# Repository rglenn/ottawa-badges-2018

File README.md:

# ottawa-badges-2018
Maker badges for Maker Faire Ottawa 2018

More information is available on the [wiki](https://github.com/rglenn/ottawa-badges-2018/wiki) - please check there!

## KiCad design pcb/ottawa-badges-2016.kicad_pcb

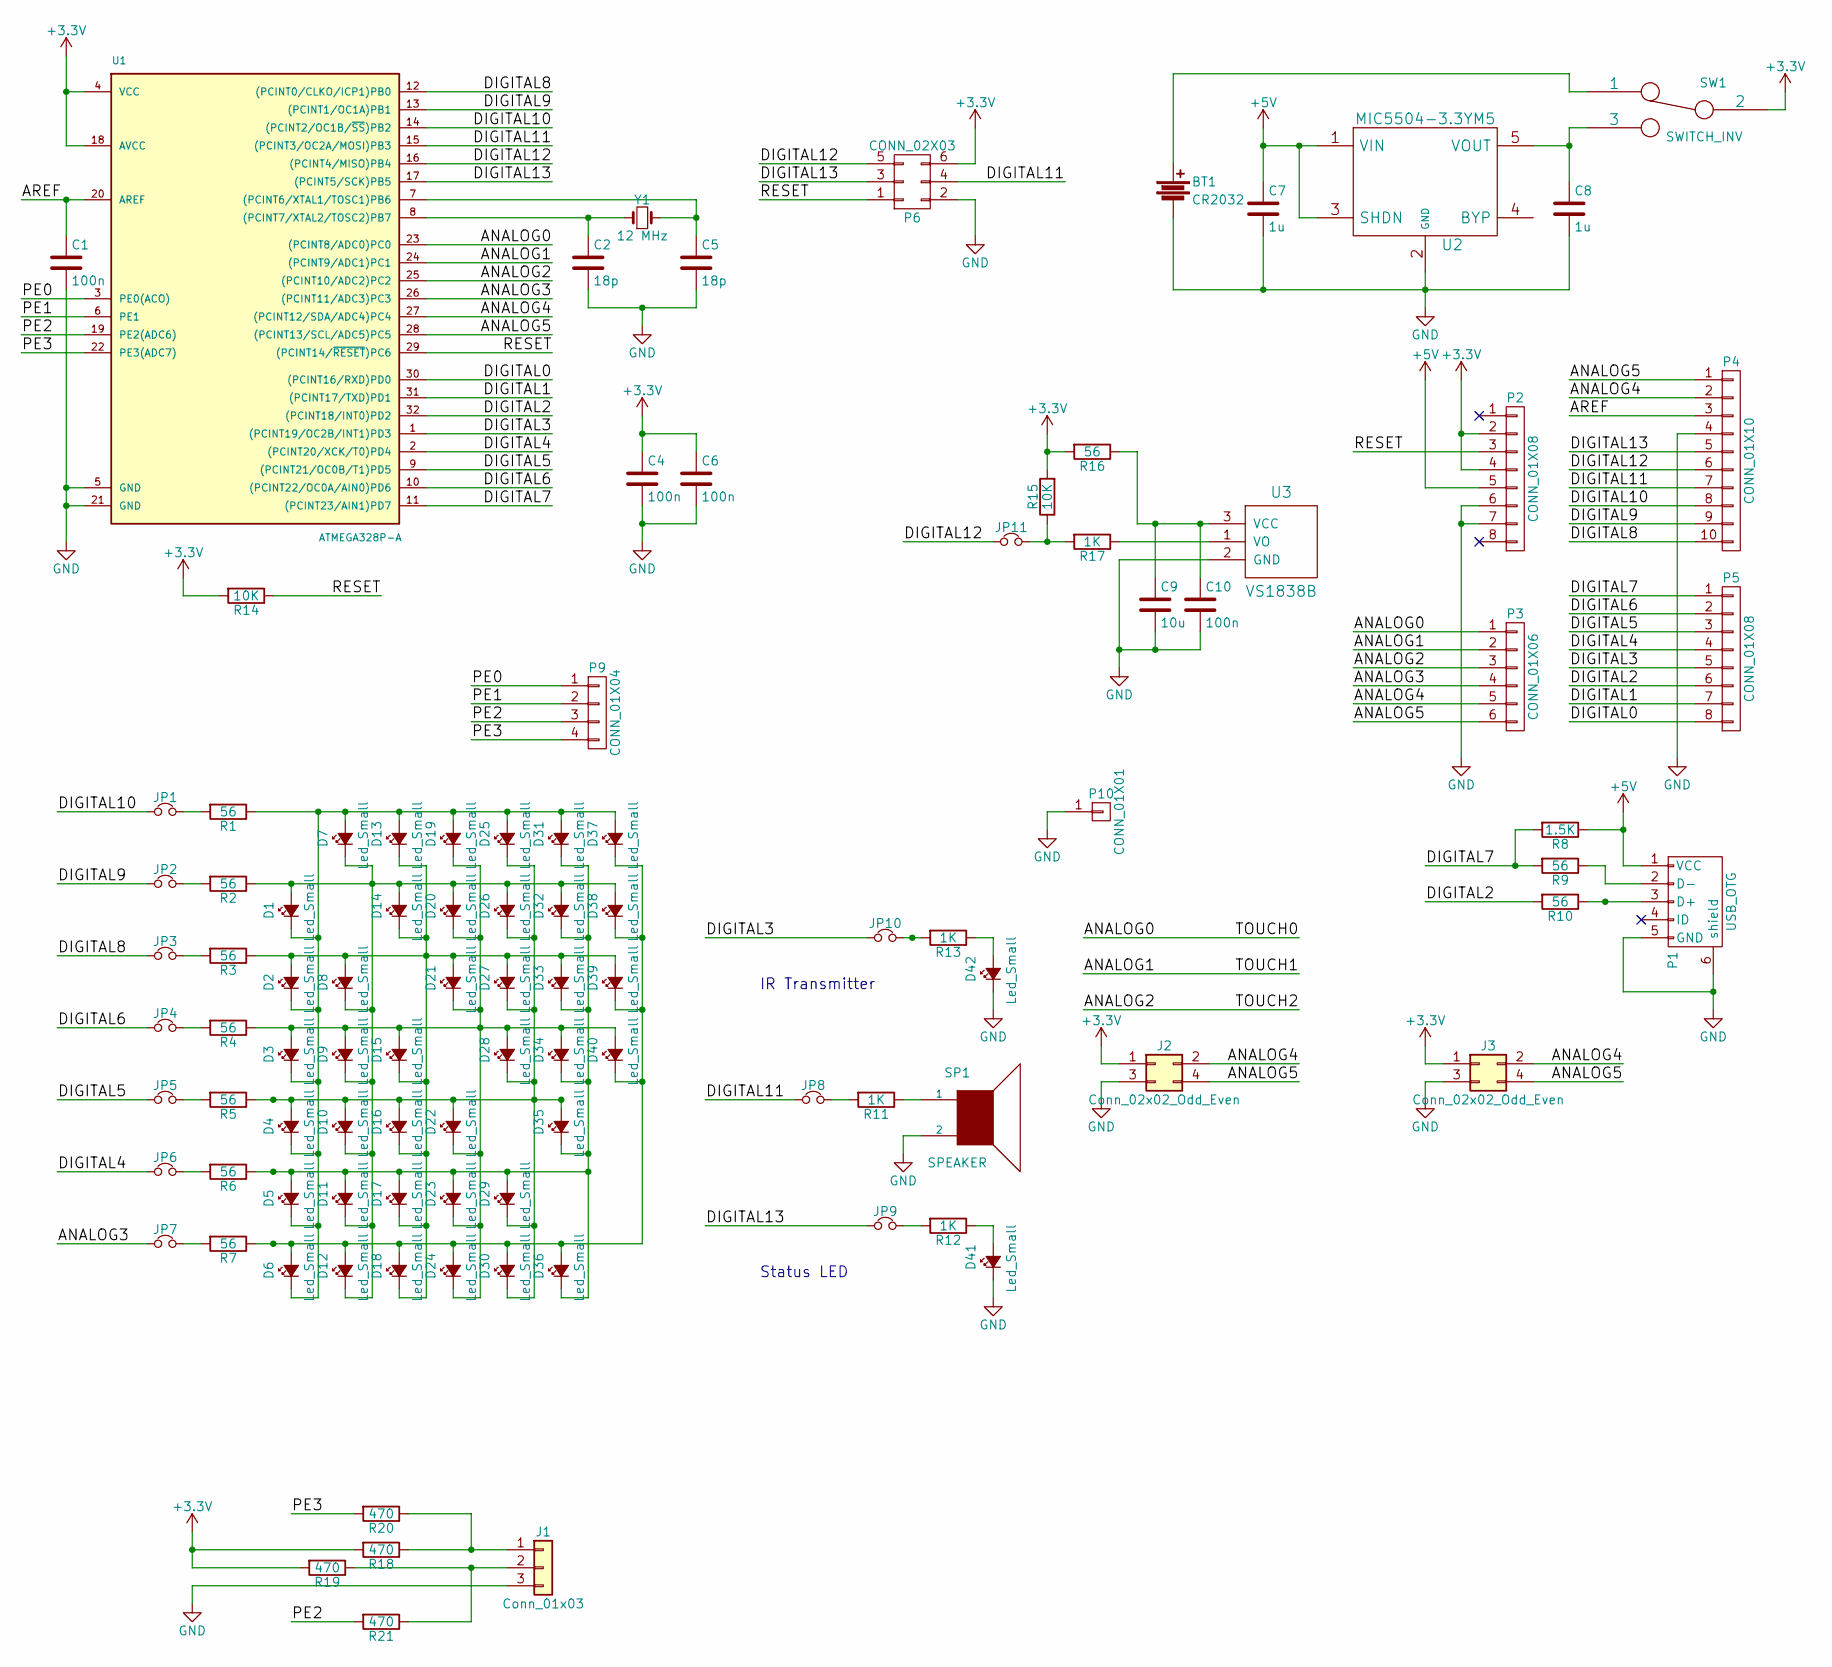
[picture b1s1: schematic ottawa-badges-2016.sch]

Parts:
BT1: CR2032; CR2032-SHRAPNEL
C1, C4, C6, C10: 100n; C_0603
C2, C5: 18p; C_0603
C7, C8: 1u; C_0603
C9: 10u; C_0805
D1, D2, D3, D4, D5, D6, D7, D8, D9, D10, D11, D12, D13, D14, D15, D16, D17, D18, D19, D20, D21, D22, D23, D24, D25, D26, D27, D28, D29, D30, D31, D32, D33, D34, D35, D36, D37, D38, D39, D40, D41: Led_Small; LED_0603
D42: Led_Small; LED_0805
J1: Conn_01x03; Pin_Header_Straight_1x03_Pitch2.54mm
J2, J3: Conn_02x02_Odd_Even; Pin_Header_Straight_2x02_Pitch2.54mm
JP1, JP2, JP3, JP4, JP5, JP6, JP7, JP8, JP9, JP10, JP11: Jumper_NC_Small; SJ2
P1: USB_OTG; 10118192-0001LF
P2, P5: CONN_01X08; Socket_Strip_Straight_1x08
P3: CONN_01X06; Socket_Strip_Straight_1x06
P4: CONN_01X10; Socket_Strip_Straight_1x10
P6: CONN_02X03; Socket_Strip_Straight_2x03
P9: CONN_01X04; Socket_Strip_Straight_1x04
P10: CONN_01X01; MountingHole_4mm_Pad_Via
R1, R2, R3, R4, R5, R6, R7, R9, R10, R16: 56; R_0603
R8: 1.5K; R_0603
R11, R12, R13, R17: 1K; R_0603
R14, R15: 10K; R_0603
R18, R19, R20, R21: 470; R_0603
SP1: SPEAKER; Buzzer_12x9.5RM7.6
SW1: SWITCH_INV; MK-12C02
U1: ATMEGA328P-A; TQFP-32_7x7mm_Pitch0.8mm
U2: MIC5504-3.3YM5; SOT-23-5
U3: VS1838B; VS1838B-HORIZ
Y1: 12 MHz; crystal_FA238-TSX3225

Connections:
+3V3: C4.1, C6.1, J2.1, J3.1, P2.2, P2.4, P6.6, R14.2, R15.2, R16.2, R18.2, R19.2, SW1.2, U1.4 (VCC), U1.18 (AVCC)
+5V: C7.1, P1.1 (VCC), P2.5, R8.1, U2.1 (VIN), U2.3 (SHDN)
/ANALOG0: P3.1, U1.23 ((PCINT8/ADC0)PC0)
/ANALOG1: P3.2, U1.24 ((PCINT9/ADC1)PC1)
/ANALOG2: P3.3, U1.25 ((PCINT10/ADC2)PC2)
/ANALOG3: JP7.1, P3.4, U1.26 ((PCINT11/ADC3)PC3)
/ANALOG4: J2.2, J3.2, P3.5, P4.2, U1.27 ((PCINT12/SDA/ADC4)PC4)
/ANALOG5: J2.4, J3.4, P3.6, P4.1, U1.28 ((PCINT13/SCL/ADC5)PC5)
/AREF: C1.1, P4.3, U1.20 (AREF)
/DIGITAL0: P5.8, U1.30 ((PCINT16/RXD)PD0)
/DIGITAL1: P5.7, U1.31 ((PCINT17/TXD)PD1)
/DIGITAL2: P5.6, R10.2, U1.32 ((PCINT18/INT0)PD2)
/DIGITAL3: JP10.1, P5.5, U1.1 ((PCINT19/OC2B/INT1)PD3)
/DIGITAL4: JP6.1, P5.4, U1.2 ((PCINT20/XCK/T0)PD4)
/DIGITAL5: JP5.1, P5.3, U1.9 ((PCINT21/OC0B/T1)PD5)
/DIGITAL6: JP4.1, P5.2, U1.10 ((PCINT22/OC0A/AIN0)PD6)
/DIGITAL7: P5.1, R8.2, R9.2, U1.11 ((PCINT23/AIN1)PD7)
/DIGITAL8: JP3.1, P4.10, U1.12 ((PCINT0/CLKO/ICP1)PB0)
/DIGITAL9: JP2.1, P4.9, U1.13 ((PCINT1/OC1A)PB1)
/DIGITAL10: JP1.1, P4.8, U1.14 ((PCINT2/OC1B/~SS~)PB2)
/DIGITAL11: JP8.1, P4.7, P6.4, U1.15 ((PCINT3/OC2A/MOSI)PB3)
/DIGITAL12: JP11.1, P4.6, P6.5, U1.16 ((PCINT4/MISO)PB4)
/DIGITAL13: JP9.1, P4.5, P6.3, U1.17 ((PCINT5/SCK)PB5)
/PE0: P9.1, U1.3 (PE0(ACO))
/PE1: P9.2, U1.6 (PE1)
/PE2: P9.3, R21.2, U1.19 (PE2(ADC6))
/PE3: P9.4, R20.2, U1.22 (PE3(ADC7))
/RESET: P2.3, P6.1, R14.1, U1.29 ((PCINT14/~RESET~)PC6)
GND: BT1.2, C1.2, C2.2, C4.2, C5.2, C6.2, C7.2, C8.2, C9.2, C10.2, D41.1 (K), D42.1 (K), J1.3, J2.3, J3.3, P1.5 (GND), P1.6 (shield), P2.6, P2.7, P4.4, P6.2, P10.1, SP1.2, U1.5 (GND), U1.21 (GND), U2.2 (GND), U3.2 (GND)
unnamed: BT1.1, SW1.1
unnamed: C2.1, U1.8 ((PCINT7/XTAL2/TOSC2)PB7), Y1.1
unnamed: C5.1, U1.7 ((PCINT6/XTAL1/TOSC1)PB6), Y1.2
unnamed: C8.1, SW1.3, U2.5 (VOUT)
unnamed: C9.1, C10.1, R16.1, U3.3 (VCC)
unnamed: D1.1 (K), D2.1 (K), D3.1 (K), D4.1 (K), D5.1 (K), D6.1 (K), D7.2 (A), D13.2 (A), D19.2 (A), D25.2 (A), D31.2 (A), D37.2 (A), R1.1
unnamed: D1.2 (A), D7.1 (K), D8.1 (K), D9.1 (K), D10.1 (K), D11.1 (K), D12.1 (K), D14.2 (A), D20.2 (A), D26.2 (A), D32.2 (A), D38.2 (A), R2.1
unnamed: D4.2 (A), D10.2 (A), D16.2 (A), D22.2 (A), D25.1 (K), D26.1 (K), D27.1 (K), D28.1 (K), D29.1 (K), D30.1 (K), D35.2 (A), R5.1
unnamed: D5.2 (A), D11.2 (A), D17.2 (A), D23.2 (A), D29.2 (A), D31.1 (K), D32.1 (K), D33.1 (K), D34.1 (K), D35.1 (K), D36.1 (K), R6.1
unnamed: D6.2 (A), D12.2 (A), D18.2 (A), D24.2 (A), D30.2 (A), D36.2 (A), D37.1 (K), D38.1 (K), D39.1 (K), D40.1 (K), R7.1
unnamed: D2.2 (A), D8.2 (A), D13.1 (K), D14.1 (K), D15.1 (K), D16.1 (K), D17.1 (K), D18.1 (K), D21.2 (A), D27.2 (A), D33.2 (A), D39.2 (A), R3.1
unnamed: D3.2 (A), D9.2 (A), D15.2 (A), D19.1 (K), D20.1 (K), D21.1 (K), D22.1 (K), D23.1 (K), D24.1 (K), D28.2 (A), D34.2 (A), D40.2 (A), R4.1
unnamed: D41.2 (A), R12.1
unnamed: D42.2 (A), R13.1
unnamed: J1.1, R18.1, R20.1
unnamed: J1.2, R19.1, R21.1
unnamed: JP1.2, R1.2
unnamed: JP2.2, R2.2
unnamed: JP3.2, R3.2
unnamed: JP4.2, R4.2
unnamed: JP5.2, R5.2
unnamed: JP6.2, R6.2
unnamed: JP7.2, R7.2
unnamed: JP8.2, R11.2
unnamed: JP9.2, R12.2
unnamed: JP10.2, R13.2
unnamed: JP11.2, R15.1, R17.2
unnamed: P1.2 (D-), R9.1
unnamed: P1.3 (D+), R10.1
unnamed: R11.1, SP1.1
unnamed: R17.1, U3.1 (VO)

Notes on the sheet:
IR Transmitter
Status LED

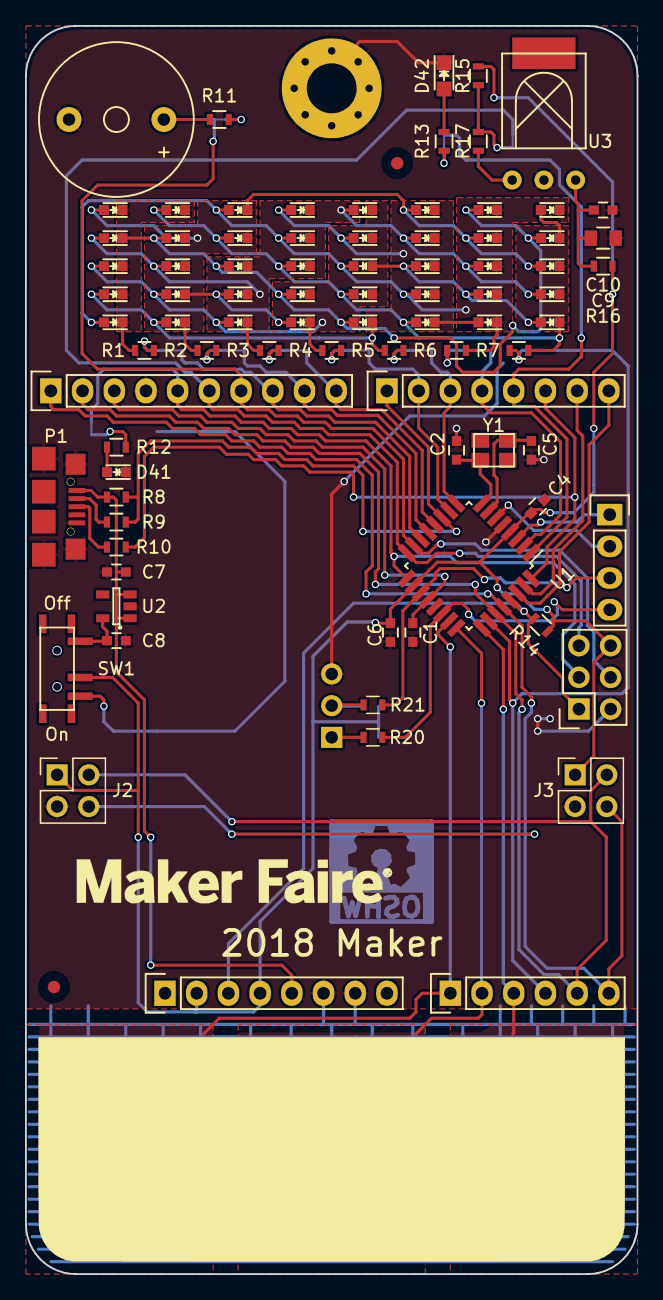
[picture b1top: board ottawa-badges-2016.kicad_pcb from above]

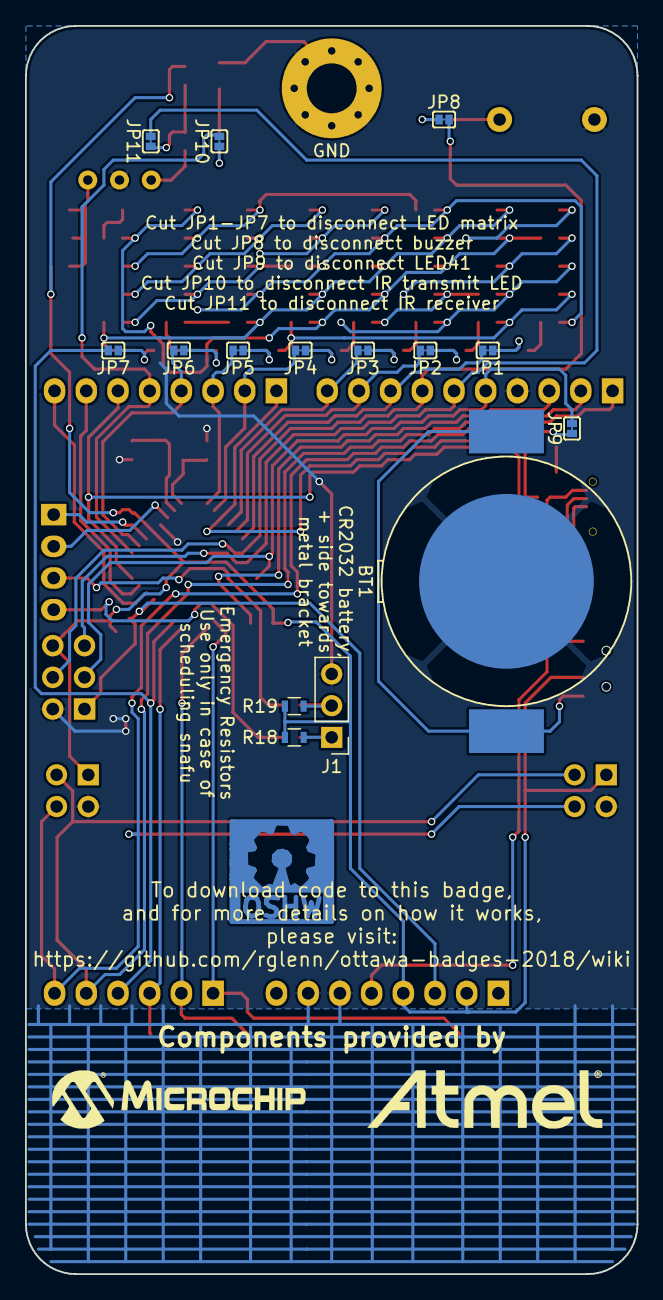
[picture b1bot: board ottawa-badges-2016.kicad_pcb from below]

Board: 2 copper layers, 49.0 x 100.0 mm, 101 parts (15 on the bottom side), 60 nets.

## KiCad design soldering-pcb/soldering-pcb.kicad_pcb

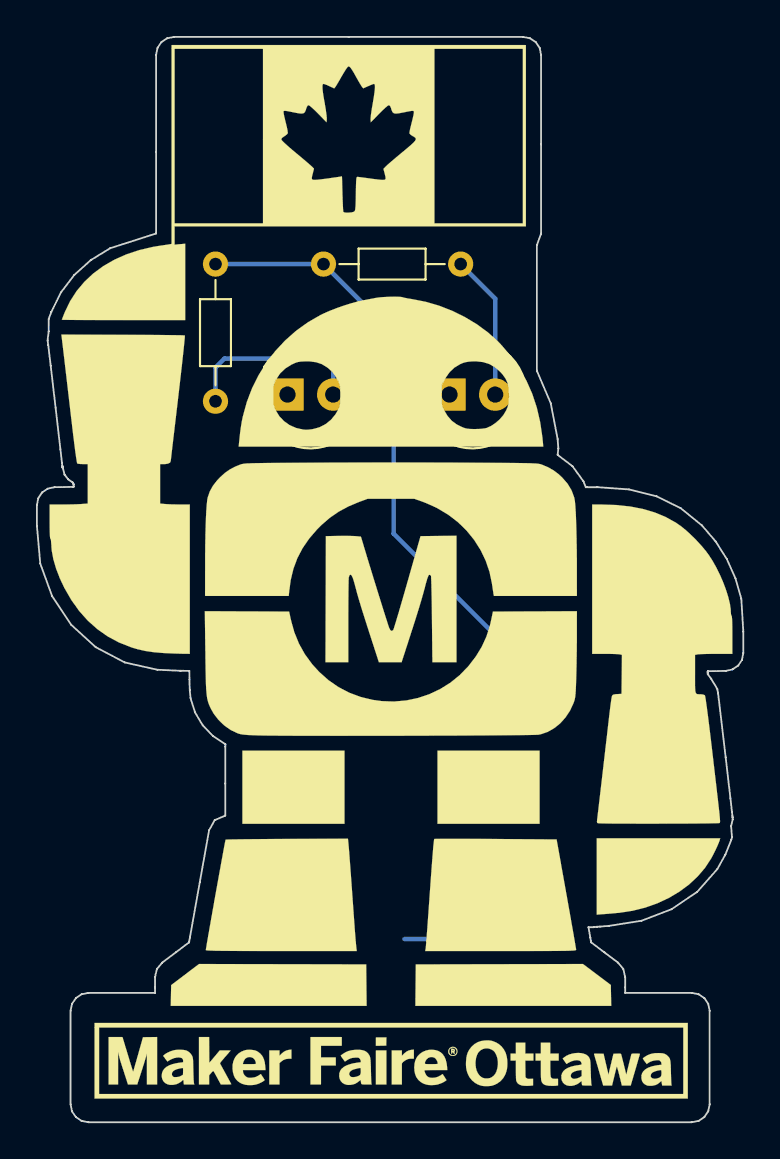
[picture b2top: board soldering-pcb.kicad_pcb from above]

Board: 2 copper layers, 39.2 x 60.3 mm, 5 parts (1 on the bottom side), 4 nets.

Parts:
BT1: Battery_Cell; CR2032-SHRAPNEL
D1, D2: LED; LED_D5.0mm
R1, R2: 470; R_Axial_DIN0204_L3.6mm_D1.6mm_P7.62mm_Horizontal

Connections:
unnamed: BT1.1, R1.1, R2.1
unnamed: BT1.2, D1.1, D2.1
unnamed: D1.2, R1.2
unnamed: D2.2, R2.2

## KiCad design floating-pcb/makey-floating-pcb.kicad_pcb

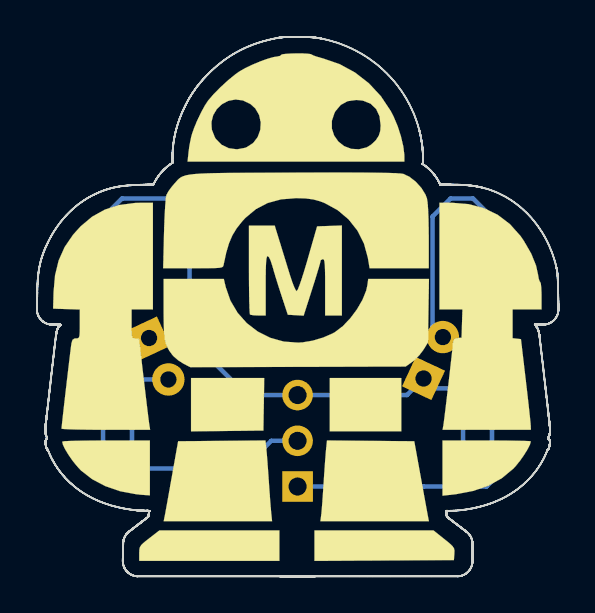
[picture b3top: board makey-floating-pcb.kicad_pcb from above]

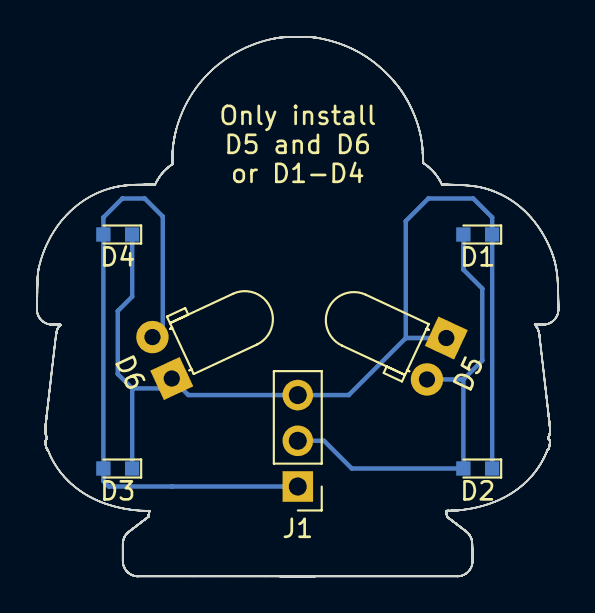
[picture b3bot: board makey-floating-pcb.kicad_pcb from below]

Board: 2 copper layers, 29.0 x 30.0 mm, 7 parts (7 on the bottom side), 3 nets.

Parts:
D1, D2, D3, D4: LED; LED_0603
D5, D6: LED; LED_D3.0mm_Horizontal_O1.27mm_Z2.0mm
J1: Conn_01x03; Pin_Header_Straight_1x03_Pitch2.54mm

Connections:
unnamed: D1.1, D2.1, D3.1, D4.1, D5.1, D6.1, J1.3
unnamed: D1.2, D2.2, D5.2, J1.2
unnamed: D3.2, D4.2, D6.2, J1.1

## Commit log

2018-05-19 Initial import from 2016 files
2018-10-02 Adding note about Wiki to readme
2018-10-16 Adding all latest files.
